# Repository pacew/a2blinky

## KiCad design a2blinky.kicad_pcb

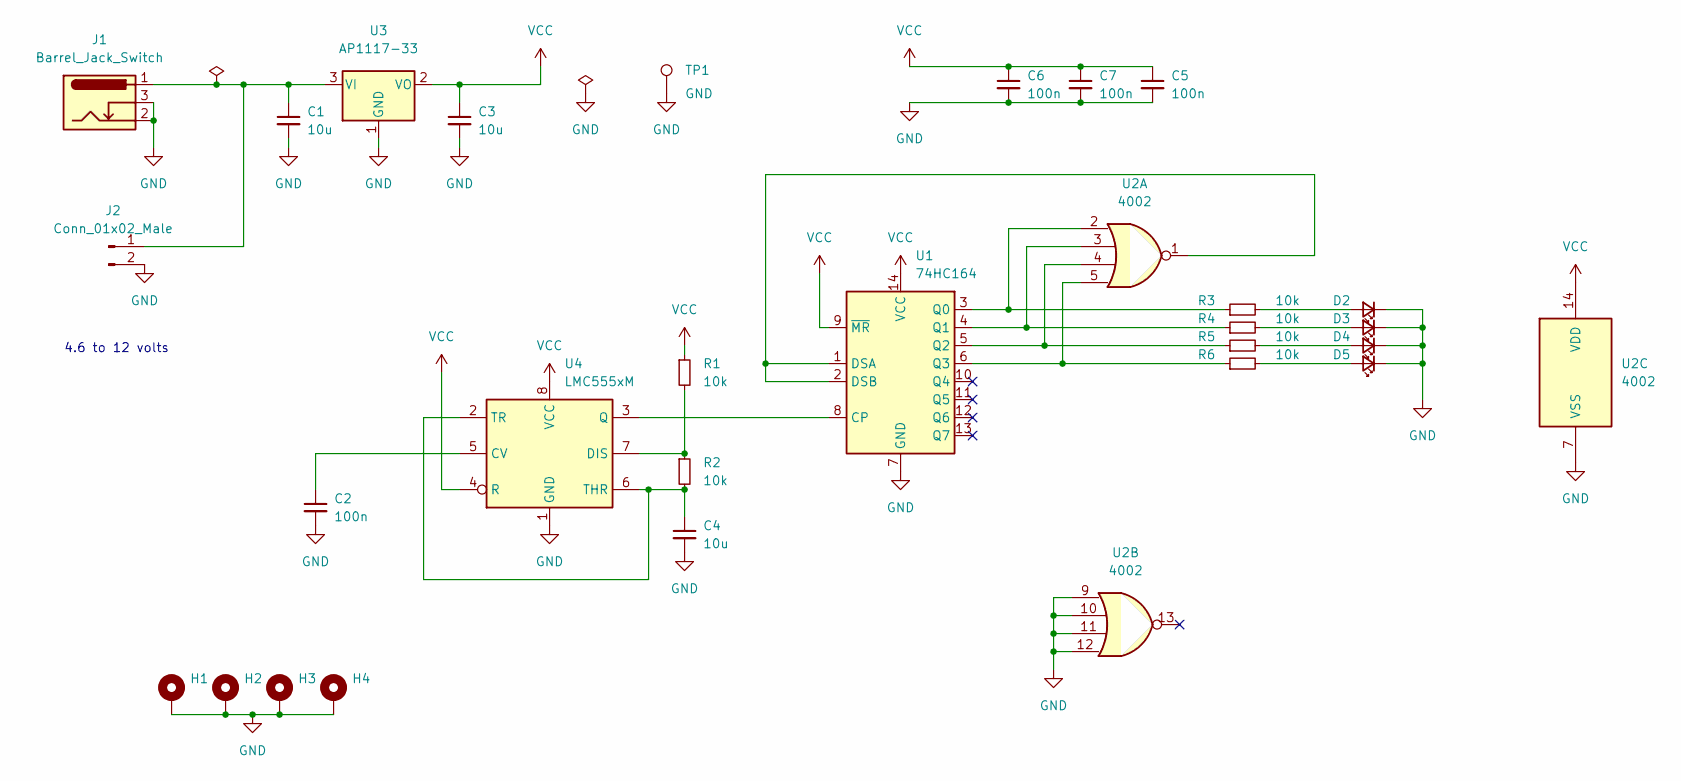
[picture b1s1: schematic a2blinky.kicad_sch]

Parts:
C1, C3, C4: 10u; C_0805_2012Metric; LCSC C15850
C2, C5, C6, C7: 100n; C_0805_2012Metric; LCSC C49678
D2, D3, D4, D5: LED_Small; LED_0805_2012Metric; LCSC C2297
H1, H2, H3, H4: MountingHole_Pad; MountingHole_3.5mm_Pad
J1: Barrel_Jack_Switch; BarrelJack_Horizontal; LCSC C194407
J2: Conn_01x02_Male; PinHeader_1x02_P2.54mm_Vertical
R1, R2, R3, R4, R5, R6: 10k; R_0805_2012Metric; LCSC C17414
TP1: GND; PinHeader_1x01_P2.54mm_Vertical
U1: 74HC164; SOIC-14_3.9x8.7mm_P1.27mm; LCSC C6825
U2: 4002; SOIC-14_3.9x8.7mm_P1.27mm
U3: AP1117-33; SOT-223-3_TabPin2; LCSC C6186
U4: LMC555xM; SOIC-8_3.9x4.9mm_P1.27mm; LCSC C90760

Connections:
GND: C1.2, C2.2, C3.2, C4.2, C5.2, C6.2, C7.2, D2.1 (K), D3.1 (K), D4.1 (K), D5.1 (K), H1.1, H2.1, H3.1, H4.1, J1.2, J1.3, J2.2, TP1.1, U1.7 (GND), U2.7 (VSS), U2.9, U2.10, U2.11, U2.12, U3.1 (GND), U4.1 (GND)
unnamed: C1.1, J1.1, J2.1, U3.3 (VI)
unnamed: C2.1, U4.5 (CV)
unnamed: C4.1, R2.2, U4.2 (TR), U4.6 (THR)
unnamed: D2.2 (A), R3.2
unnamed: D3.2 (A), R4.2
unnamed: D4.2 (A), R5.2
unnamed: D5.2 (A), R6.2
unnamed: R1.2, R2.1, U4.7 (DIS)
unnamed: R3.1, U1.3 (Q0), U2.2
unnamed: R4.1, U1.4 (Q1), U2.3
unnamed: R5.1, U1.5 (Q2), U2.4
unnamed: R6.1, U1.6 (Q3), U2.5
unnamed: U1.1 (DSA), U1.2 (DSB), U2.1
unnamed: U1.8 (CP), U4.3 (Q)
VCC: C3.1, C5.1, C6.1, C7.1, R1.1, U1.9 (~MR), U1.14 (VCC), U2.14 (VDD), U3.2 (VO), U4.4 (R), U4.8 (VCC)

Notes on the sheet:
4.6 to 12 volts

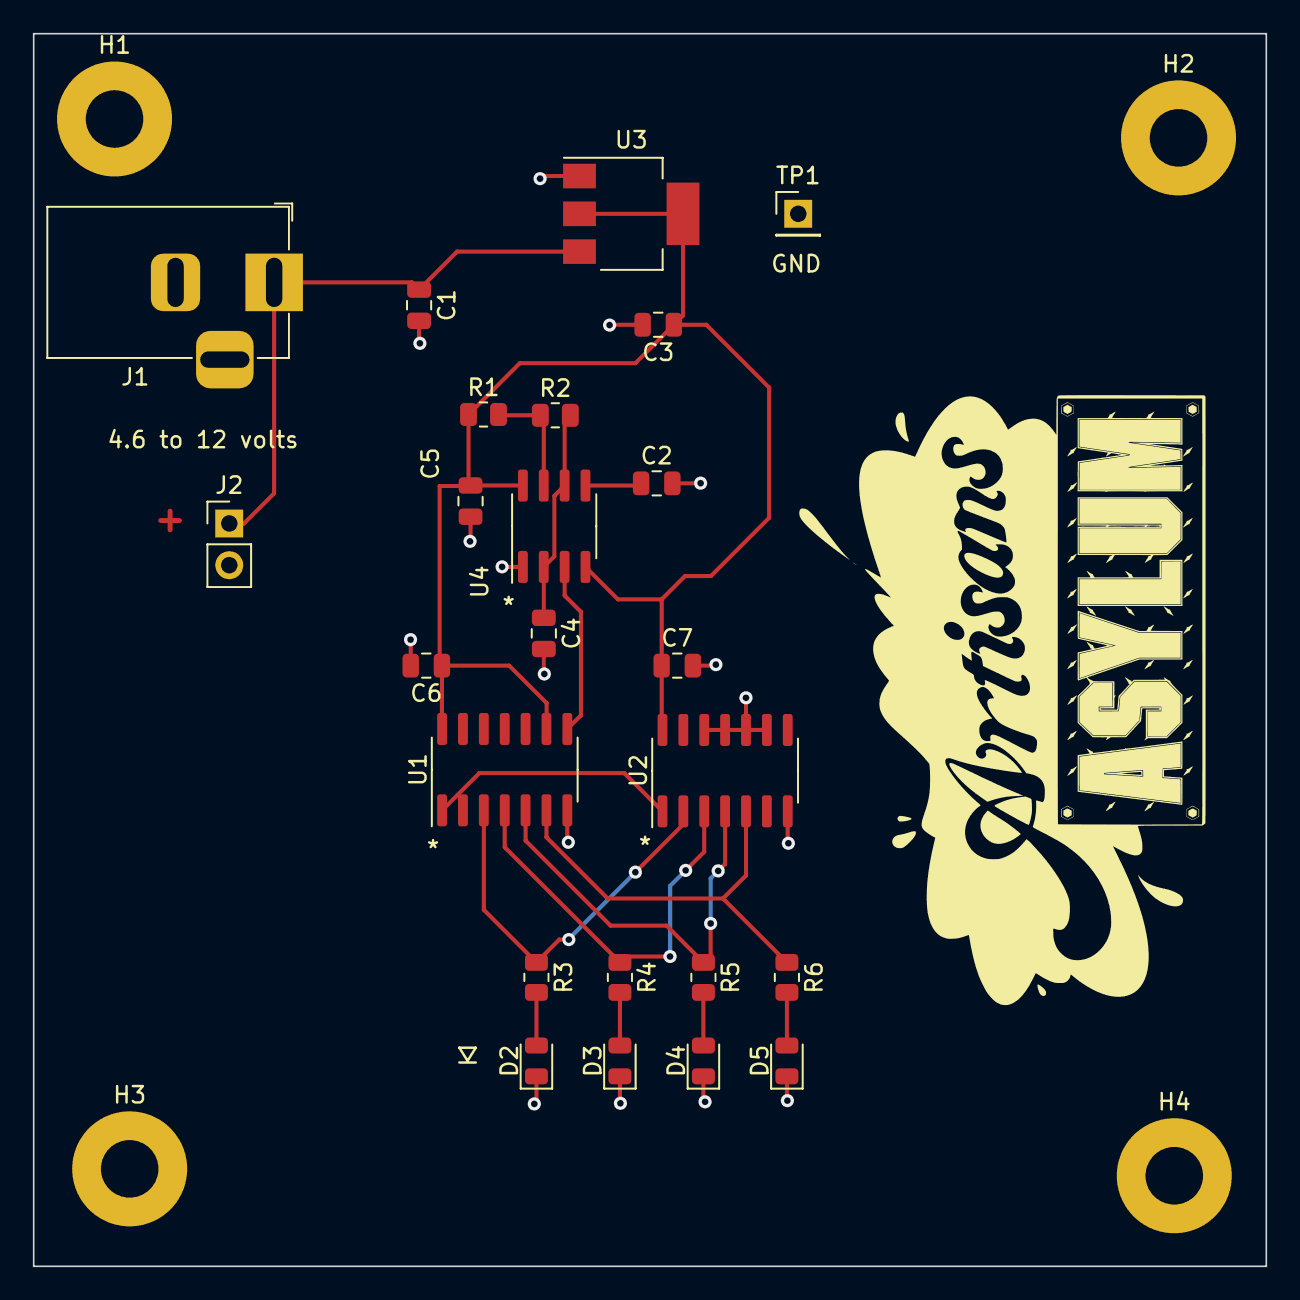
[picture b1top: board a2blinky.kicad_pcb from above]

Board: 2 copper layers, 75.0 x 75.0 mm, 28 parts (0 on the bottom side), 16 nets.

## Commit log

2022-10-19 start
2022-10-26 cleanup
2022-12-15 ecos
2022-12-17 silkscreen
2022-12-22 polish
2023-01-05 notes
2023-01-07 setup
2023-01-12 parts
2023-01-12 step3
2023-01-12 snapshot
